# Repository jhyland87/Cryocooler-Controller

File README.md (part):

# ESP32-S3 Cryocooler Controller

Firmware for an ESP32-S3 DevKit that automates the cooldown sequence of a cryogenic cooler. The controller manages a compressor-driven cold stage through ten operational states — from a cold start at room temperature (~295 K) down to an operating setpoint of 78 K, with a graceful shutdown sequence — while enforcing thermal safety limits, detecting back-EMF current spikes, streaming live telemetry via Protobuf over WebSocket, and serving a real-time Preact dashboard over WiFi.

---

## Hardware

| Component | Part | Interface | Address / Pin | Purpose |
|-----------|------|-----------|---------------|---------|
| Microcontroller | ESP32-S3 DevKitC-1-N32R16V | — | — | Host MCU (32 MB flash, 16 MB PSRAM) |
| Cold-stage sensor | ADS1220 + PT1000 RTD | SPI mode 1 (main bus) | CS: decoder Y6 | Cold-stage temperature (4-wire, ratiometric) |
| Waveform generator | AD9837 DDS (AD9833 register set, 16 MHz clock) | SPI (main bus) | FSYNC (CS): decoder Y0 | 60 Hz sine wave for compressor |
| DAC | AD5453 14-bit multiplying | SPI mode 1 (main bus), write only | SYNC: decoder Y1 | Amplifier amplitude control |
| Power monitor | INA239 + 15 mΩ shunt | SPI mode 1 (main bus) | CS: decoder Y2, ALERT: expander GP6 | 12 V rail voltage, current and power |
| IMU | LSM6DSOX on the cryocooler: its own 18 x 18 mm board (`hardware/kicad/imu/`, not yet built) or the Adafruit breakout it replaces | SPI (main bus) via header J14 | CS: decoder Y7, INT1: GPIO 2, INT2: GPIO 39 | Vibration / overstroke detection |
| Fan / pump | 4-pin PWM through a BSS138DW dual driver | LEDC PWM + PCNT tach | PWM: GPIO 9 / 14, tach: GPIO 15 / 21 | Cooling fan + pump |
| Current sensor | ACS37800-015B5 (±15 A) behind an ISOW7741 isolator | SPI mode 3 (main bus, through two gates) | CS: GPIO 17 | Amplifier AC current monitoring |
| Compressor relay | BSS138 → BSS84 high-side +12 V switch (130 mA max) | GPIO | GPIO 16 | Compressor relay on/off |
| Amplifier relay | BSS138 → BSS84 high-side switch | GPIO | GPIO 6 | Amplifier REM line on/off |
| Coolant flow sensor | Alphacool ES (Hall-effect) | GPIO | GPIO 18 | Coolant flow pulses |
| Coolant temperature | NTC thermistor | ADC | GPIO 4 | Coolant temp via voltage divider |
| Status LED | WS2812B-2020 RGB | GPIO | GPIO 38 | Fault / Ready indication |
| Expander | MCP23S08 | SPI (main bus) | CS: decoder Y3 | ±15 V flags, backlight, INA239 ALERT, touch IRQ, 3 spare pins |
| Power button | LTC2954 INT# / KILL# | GPIO | GPIO 1 / GPIO 10 | Button press ramps down, then cuts system power |
| General-purpose I/O | 2-pin headers J16-J20 (signal, GND), each with an LED that follows the pin voltage | GPIO; ADC on IO5 / IO7 only | GPIO 5, 7, 11, 12, 13 | Spare 3.3 V inputs or outputs (sensors, relay triggers, LEDs) |

**I2C:** none. Every peripheral is on SPI or a GPIO.

**Main SPI bus:** CLK → GPIO 42, MOSI → GPIO 41, MISO → GPIO 40. Devices: AD9837, AD5453, the LSM6DSOX (on a cable, header J14), INA239, ADS1220, MCP23S08, display, touch controller and the ACS37800. Their chip selects come from the SN74LVC138A decoder, driven from GPIO 3, 44, 45 and 8. The INA239, ADS1220 and AD5453 use SPI mode 1, and the INA239 and ADS1220 data outputs are high-impedance while CS is high. The ADS1220 DRDY pin is not wired to the MCU.

**ACS37800:** on the main SPI bus, with CS on GPIO 17 (a plain GPIO, not a decoder output). The ACS37800 keeps MISO driven when CS is high, so two SN74LVC1G125 gates connect it only while CS is low: one passes SCK to the isolator, the other passes its MISO to the bus. See [`docs/acs37800.md`](docs/acs37800.md) for its SPI frame and bring-up gotchas.

**General-purpose I/O:** each of the five pins has 100 Ω in series, 200 kΩ to ground (the LED driver's divider) and an ESD clamp, and is 3.3 V only. GPIO 5 and 7 are ADC1 and can read analog with WiFi on; GPIO 11-13 are ADC2, so digital only. The firmware defines the pins (`AUX_IO*_PIN`) but does not use them yet.

**Fan and pump:** each PWM GPIO drives a BSS138 (GPIO high = PWM line low = 0 % drive), because the fan PWM line can reach 5.25 V. A 10 kΩ gate pull-up holds 0 % drive during boot. Each tach line has a 4.7 kΩ series resistor, a clamp on the GPIO side, and a 4.7 kΩ pull-up to 3.3 V.

**INA239 ALERT:** drives its red LED only; it is not wired to the MCU, and the firmware does not read it.

### Circuit board

The 130 x 110 mm 4-layer board is generated from the KiCad schematic in [`hardware/kicad/`](hardware/kicad/README.md). Each module has its own outlined, labelled box on the silkscreen, and the sections with their own supply jumper and LED can be switched off one at a time.

---

## Architecture

All subsystem modules follow a standardised lifecycle pattern built on a CRTP base class (`ModuleBase<T>`) with compile-time interface enforcement. Modules are registered in declarative arrays and initialised/serviced via generic helpers — adding a new module is a one-liner. See [`docs/modules.md`](docs/modules.md) for the full module authoring guide.

```mermaid
flowchart TD
    subgraph Persistent ["Persistent Modules (init once at startup)"]
        HW[hardware<br/>SPI buses]
        IMU[imu<br/>LSM6DSOX accelerometer]
        CMD[commands<br/>Serial console]
        DASH[dashboard<br/>WiFi + Preact SPA + WebSocket]
        TEL[telemetry<br/>Protobuf frame builder]
        SYS[sysinfo<br/>INA239 power monitor]
        OTA[ota<br/>HTTP firmware updates]
    end

    subgraph Control ["Control Modules (re-init on every Initialize state)"]
        COOL[cooling<br/>PWM fan + pump<br/>software LUT]
        CH[cold_head<br/>ADS1220 PT1000 RTD]
        AMP[amplifier<br/>AD9837 + AD5453 DAC + ACS37800]
        COMP[compressor<br/>relay GPIO]
        IND[indicator<br/>WS2812 RGB LED]
    end

    subgraph FSM ["Core Logic"]
        SM[state_machine<br/>Pure FSM — no hardware calls]
    end

    CH  -->|tempC, coolingRate, stalled| SM
    AMP -->|rmsV, overstroke| SM
    IMU -->|overstroke| SM
    SYS -->|sysVoltage| SM

    SM -->|dacTarget| AMP
    SM -->|compressorRelay, amplifierRelay| COMP
    SM -->|faultIndMode, readyIndMode| IND
    SM -->|Output| TEL

    TEL --> DASH
    TEL --> CMD

    classDef persistent fill:#dbeafe,stroke:#3b82f6,color:#1e3a5f
    classDef control    fill:#dcfce7,stroke:#16a34a,color:#14532d
    classDef fsm        fill:#fef3c7,stroke:#d97706,color:#78350f

    class HW,IMU,CMD,DASH,TEL,SYS,OTA persistent
    class COOL,CH,AMP,COMP,IND control
    class SM fsm

    style Persistent fill:#eff6ff,stroke:#93c5fd
    style Control    fill:#f0fdf4,stroke:#86efac
    style FSM        fill:#fffbeb,stroke:#fcd34d
```

---

## Module Reference

### hardware

Initialises the main SPI bus (`SPI.begin(...)`), which the ACS37800 shares.

---

### state_machine

The core of the controller. Ingests sensor readings every tick and outputs a complete set of actuator targets. Contains no hardware calls — pure logic, fully unit-testable on the host PC.

**States:**

| # | Name | Description | FAULT LED | READY LED | DAC |
|---|------|-------------|-----------|-----------|-----|
| -1 | Off | System powered down | Off | Off | 0 |
| 0 | Initialize | Power-up self-check | Solid Amber | Solid Amber | 0 |
| 1 | Idle | Warm standby | Solid Red | Off | 0 |
| 2 | CoarseCooldown | Cooling above 85 K | Flash Fast Red | Off | proportional to temp |
| 3 | FineCooldown | Cooling below 85 K | Flash Fast Red | Flash Slow Green | proportional to temp |
| 4 | Overshoot | Below setpoint, settling | Flash Fast Red | Flash Fast Green | 0 |
| 5 | Settle | In setpoint band; Normal relay | Flash Fast Red | Flash Fast Green | 0 |
| 6 | Baseline | Collecting pre-run baseline (5 min) | Off | Solid Green | 0 |
| 7 | Operating | Normal cryogenic operation | Off | Solid Green | 0 |
| 8 | Shutdown | Graceful shutdown; DAC ramps down | Off | Off | ramps → 0 |
| 9 | Delay | Timed hold; resumes at configured next state | Solid Amber | Solid Amber | 0 |
| 127 | Fault | Terminal fault state | Flash Fast Red | Off | 0 |

**Key configuration** (all in `config.h`):

| Constant | Default | Description |
|----------|---------|-------------|
| `SETPOINT_C` | -195.15 °C (78 K) | Target cold-stage temperature |
| `COARSE_FINE_THRESHOLD_C` | -188.15 °C (85 K) | Coarse/Fine transition boundary |
| `SETPOINT_TOLERANCE_C` | 3.0 °C | Band around setpoint for settle/overshoot logic |
| `SETTLE_DURATION_MS` | 60 000 ms | Time stable before advancing to Baseline |
| `BASELINE_DURATION_MS` | 300 000 ms | Baseline collection window |
| `SHUTDOWN_DURATION_MS` | 5 000 ms | Graceful shutdown ramp duration |
| `STALL_DETECT_WINDOW_MS` | 600 000 ms | Stall detection observation window |
| `STALL_MIN_DROP_C` | 2.0 °C | Minimum temp drop required in the window |
| `BACKOFF_MAX_COUNT` | 10 | Max overstroke events before TooManyBackoffs fault |

---

### cold_head

Reads the PT1000 RTD via the ADS1220 24-bit ADC over SPI (mode 1, chip select GPIO 44). The ADC is configured for 4-wire ratiometric measurement (gain 1, PGA bypassed, 20 SPS with simultaneous 50/60 Hz rejection) with 250 µA IDAC excitation and a 3854 Ω external reference resistor. Raw ADC counts are converted to resistance, then to temperature via the Callendar-Van Dusen equation (above 0 °C) and AN709 polynomial (below 0 °C).

Uses a non-blocking two-phase state machine: start single-shot conversion → wait out the 50 ms conversion time (DRDY is not wired) → read the 24-bit result. Maintains a ring buffer of `TEMP_HISTORY_SIZE` timestamped samples for cooling-rate calculation (°C/min), stall detection, and cooldown progress (0–100 %).

| Function | Returns |
|----------|---------|
| `getLastTempK()` | Cold-stage temperature in Kelvin |
| `getLastTempC()` | Cold-stage temperature in Celsius |
| `getCoolingRateCPerMin()` | °C/min, positive = cooling |
| `isStalled()` | True if stall threshold exceeded |

---

### amplifier

Drives the AD9837 DDS (60 Hz sine wave, through the MD_AD9833 library set to a 16 MHz clock), the AD5453 14-bit multiplying SPI DAC (amplifier amplitude), the amplifier relay (GPIO 6) and the ACS37800 current sensor. Provides two ramp modes:

- `rampToVoltage(target)` — smooth ramp at ±`DAC_MAX_STEP_PER_INTERVAL` per tick
- `rampTowardShutdown(target)` — fast ramp at ±`DAC_SHUTDOWN_STEP_PER_INTERVAL` per tick

**Overstroke (back-EMF) detection:** A slow-tracking EMA forms the baseline. A reading exceeding `baseline + OVERSTROKE_CURRENT_THRESHOLD_A` fires `hasOverstroke()`, subject to `OVERSTROKE_DEBOUNCE_MS`. The EMA is primed for `OVERSTROKE_PRIME_READINGS` ticks on startup.

---

### imu

Drives the LSM6DSOX 6-DOF IMU over SPI (CS GPIO 1) in FIFO mode at 833 Hz. The sensor is mounted on the cryocooler, so it sees the cooler body's vibration. It is cabled to header J14: the IMU board (`hardware/kicad/imu/`, not yet built) or, until then, the Adafruit breakout (product 4438); pinouts are in `hardware/kicad/README.md`. The SPI clock is `LSM6DSOX_SPI_FREQUENCY_HZ`. A missing cable is non-fatal: the module reports unavailable. On `init()` the module sets `I2C_disable` in CTRL4_C (13h) right after the driver's `begin_SPI()`, so the IMU's I²C block ignores traffic for the other devices on the shared SCK/MOSI lines (DS12814 §5.1.1; the driver only disables I3C). The sensor is then configured and a one-time blocking calibration collects samples to compute per-axis offsets (gravity is removed from the Z offset).

Each `service()` call applies calibration offsets, runs a first-order low-pass filter, and computes roll/pitch from filtered acceleration. Motion / overstroke is flagged when acceleration magnitude deviates from 9.81 m/s² by more than `ACCEL_THRESHOLD_MPS2`; it clears after `MOTION_TIMEOUT_MS` of stillness.

A periodic FFT (`calculateFrequency()`) detects the compressor vibration frequency in the 45–75 Hz band using 256 samples at 833 Hz, with Hann windowing and quadratic peak interpolation.

| Function | Returns |
|----------|---------|
| `isInitialized()` | True if sensor was found and configured |
| `hasOverstroke()` | True while motion/overstroke is active |
| `getRoll()` / `getPitch()` | Orientation angles in degrees |
| `getAccelMag()` | Calibrated acceleration magnitude (m/s²) |
| `getFrequencyHz()` | Detected compressor frequency (Hz), or NAN |
| `getTemperature()` | IMU die temperature (°C); mounted on the cooler, this is the cooler-body temperature and also feeds the "ambient" value |

---

### sysinfo

Reads the 12 V rail voltage, current and power from the INA239 power monitor over SPI (15 mΩ shunt, 10 A calibration; GPIO 3 chip select) and exposes `getVoltage()`, `getCurrent()` and `getPower()`. SPI has no ACK, so each tick first reads the INA239 manufacturer and device ID registers; after 3 consecutive failures (for example when 12 V drops) the module disables itself until `reinit`. It also tracks CPU load, heap and PSRAM.

---

### cooling

Controls the cooling fan and pump directly from the ESP32: LEDC generates 25 kHz PWM and PCNT counts the tach pulses. Also samples the Alphacool ES flow sensor and NTC coolant temperature.

**Software LUT:** Each channel has an independently-configured temperature-to-duty lookup table with hysteresis, evaluated once per second from coolant temperature. Entries are sorted ascending by temperature; the evaluator only writes to the chip when the active row changes.

**Fault detection:** A channel with drive applied and no tach pulses for `COOLING_TACH_STALL_MS` raises `hasFanFault()`. It is reported in telemetry and logs and does not fault the state machine.

**Pump normalisation:** User-facing pump speeds are 0–100 % normalised, mapped to 0–`COOLING_PUMP_MAX_DUTY_PCT` (raw 0–255) at the hardware boundary. The pump stalls above ~16 % effective duty (~4400 RPM).

**Tracking monitors:** Score-based monitors for fan duty, coolant temperature, and flow rate detect sustained deviations from expected values.

| Function | Returns |
|----------|---------|
| `getCoolantTemperature()` | Coolant temperature in °C |
| `getCoolantFlowRate()` | Coolant flow rate in L/min |
| `getFanSpeed()` | Fan duty (0–255) |
| `getFanRPM()` | Fan tachometer RPM |
| `getPumpSpeed()` | Pump speed (normalised 0–100 %) |
| `getPumpRPM()` | Pump tachometer RPM |
| `hasFanFault()` | True while a driven channel has no tach pulses |
| `getFanFaultDurationMs()` | Duration of current fault episode |

---

### compressor

Manages the compressor relay (GPIO 16 → high-side +12 V switch) with timed-run support. `compressor start <duration>` energises the relay for a specified duration (e.g. `1h30m`, `45s`), clamped to `COMPRESSOR_MAX_RUN_MS`. Can be disabled at compile time with `ENABLE_COMPRESSOR false`.

---

### indicator

Drives the on-board WS2812 RGB LED (GPIO 38) according to the state machine's requested `Mode`. All flash timing is non-blocking — `update(nowMs)` is called every loop iteration.

| Mode | Colour | Rate |
|------|--------|------|
| `SolidRed` | Red | — |
| `SolidGreen` | Green | — |
| `SolidAmber` | Amber | — |
| `FlashFastRed` | Red | 2 Hz |
| `FlashSlowGreen` | Green | 1 Hz |
| `FlashFastGreen` | Green | 2 Hz |

---

### dashboard

Connects to WiFi and serves a Preact single-page application with real-time telemetry:

- **HTTP** (port 80): serves the embedded SPA (`index.html`, `app.js`, `style.css`) and a JSON telemetry endpoint at `GET /api/telemetry`
- **WebSocket** (`ws://<hostname>/ws` on port 80): streams Protobuf-encoded telemetry frames at 1 Hz
- **mDNS**: `cryocooler.local`

The dashboard frontend uses Preact + MUI + Vite and is bundled into firmware flash at build time via `scripts/embed_web.py`. WiFi credentials live in `include/config/arduino_secrets.h`.

---

### ota

HTTP OTA firmware update endpoint. `GET /ota` serves an upload form; `POST /ota` flashes new firmware. Enabled with `ENABLE_OTA true` in `config.h`.

---

### commands

Non-blocking USB serial command handler. `service()` accumulates characters and dispatches completed lines. The same `processLine()` function is used by the TCP server and by unit tests with a stub `Print`.

| Command | Action |
|---------|--------|
| `start` | Begin cooldown (from Off or Idle) |
| `stop` | Abort and return to Idle |
| `off` | Power off the system entirely |
| `reboot` | Reboot the MCU |
| `status` | Print current state and running flag |
| `summary` | Full snapshot of all sensor and actuator values |
| `fsm state` | Print current FSM state with time-in-state |
| `fsm history` | Print recent FSM state transitions |
| `fault clear` | Clear an active fault and return to Idle |
| `fault push` | Push a fault record |
| `fault history` | Print fault log with reason and clear method |
| `board` | Print compile-time board/platform info |
| `reinit` | Re-initialise all or named modules |
| `wifi status` | Print WiFi link, signal, TX power and last disconnect reason |
| `wifi retry` | Start a new WiFi connection attempt now |
| `wifi txpower <dBm>` | Set max WiFi TX power until reboot; retries if not connected |
| `cooling on/off` | Enable / disable cooling system |
| `cooling fan <N>` | Set fan: raw duty (0–255) or percent (0–100%) |
| `cooling pump <N>` | Set pump: raw duty (0–255) or percent (0–100%) |
| `set vout <V>` | Set DAC output voltage (0–120 V, 0–100 %, or `auto`) |
| `dac raw <N>` | Raw SPI write to the AD5453 (0–16383), bypassing firmware DAC management |
| `get vout` | Get current DAC output voltage |
| `relay` | Show current state of both relays |
| `relay amplifier on/off` | Control amplifier relay |
| `relay compressor on/off` | Control compressor relay |
| `compressor start <dur>` | Start timed compressor run (e.g. `1h30m`) |
| `compressor status` | Show compressor state and remaining time |
| `compressor stop` | Stop the compressor immediately |
| `telemetry on/off` | Enable / disable telemetry output |
| `telemetry serial on/off` | Enable / disable the tab-delimited telemetry dump on USB Serial (off by default) |
| `telemetry delta on/off` | Delta-only or full frames for the serial dump |
| `dashboard on/off` | Enable / disable dashboard WebSocket broadcasts |
| `mock ...` | Sensor mock: `enable`, `disable`, `status`, `temp`, etc. |
| `log level <L>` | Set runtime log level (0–5 or off/error/warn/info/debug/verbose) |
| `shutdown` | Shut the system down |
| `ota status` | Print OTA partition and firmware version info |
| `update image` | Flash new firmware via HTTP upload |
| `help` | List all commands |

---

### telemetry

Snapshots all module values each tick into a `FrameBuilder`. The WebSocket path encodes frames as Protobuf binary via Nanopb; the HTTP `/api/telemetry` endpoint returns JSON. The schema source of truth is `proto/telemetry.proto`.

---

### frame_builder

Format-agnostic telemetry frame with a fluent field API. Renders to a tab-delimited serial line or `JsonDocument` from the same snapshot.

---

### conversions

Header-only pure-math utilities with no hardware dependencies — safe for native unit tests.

| Function | Description |
|----------|-------------|
| `resistanceToTemperaturePT1000(R)` | PT1000 Ω → °C (Callendar-Van Dusen / AN709) |
| `tempCToDacValue(...)` | Temperature → 12-bit DAC mapping |
| `tempCToFraction(...)` | Temperature → cooldown fraction [0.0, 1.0] |
| `msToHHMMSS(ms, buf)` | ms → `HH:MM:SS` string |
| `parseDurationMs(str, ...)` | Human duration string → ms (e.g. `1h30m`) |
| `formatDurationMs(ms, buf, len)` | ms → compact human string (e.g. `1h 30m 00s`) |

---

### sensor_mock

Injects synthetic sensor values into all modules for hardware-free FSM testing. When `sensor_mock::isActive()`, `read()`/`service()` in each module pull from `sensor_mock::get()` instead of hardware. Activated via the `mock` serial command.

---

## Transition Triggers

### Normal Operation Flow

`start()` selects the resume state from `tempK` and is valid from both **Off** and **Idle**. `Delay` is reachable from any non-Fault state via `startDelay()` — see [Global Transitions](#global-transitions).

```mermaid
stateDiagram-v2
    direction TB

    [*] --> Off
    Off  --> Initialize : reinit
    Idle --> Initialize : reinit
    Initialize --> Idle : init timer

    state "Cooldown Phase" as COOLDOWN {
        CoarseCooldown --> FineCooldown : temp < 85 K
        FineCooldown --> CoarseCooldown : temp > 85 K
    }

    state "Approaching Setpoint" as SETTLING {
        Overshoot --> Settle : in band
    }

    state "Stable Operation" as STABLE {
        Baseline --> Operating : baseline timer
    }

    Idle --> CoarseCooldown : start, temp <br/>≥ 85 K
    Idle --> FineCooldown   : start, below <br/>85 K
    Idle --> Overshoot      : start, below<br/> setpoint
    Idle --> Settle         : start, in band

    FineCooldown --> Overshoot : below setpoint
    FineCooldown --> Settle    : in band

    Settle --> Baseline : settle timer

    COOLDOWN --> Shutdown : stop
    SETTLING --> Shutdown : stop
    STABLE   --> Shutdown : stop
    Delay    --> Shutdown : stop
    Shutdown --> Idle     : shutdown<br/>timer

    Delay --> Idle           : timer → Idle
    Delay --> CoarseCooldown : timer → Coarse

    classDef startup  fill:#dbeafe,color:#1e3a5f
    classDef cooldown fill:#ccfbf1,color:#134e4a
    classDef settling fill:#fef3c7,color:#78350f
    classDef stable   fill:#dcfce7,color:#14532d
    classDef shutdown fill:#f1f5f9,color:#334155
    classDef delay    fill:#ede9fe,color:#3b0764

    class Off,Initialize,Idle startup
    class CoarseCooldown,FineCooldown cooldown
    class Overshoot,Settle settling
    class Baseline,Operating stable
    class Shutdown shutdown
    class Delay delay
```

### Fault Conditions

```mermaid
stateDiagram-v2
    direction LR

    state "Cooldown Phase" as COOLDOWN {
        CoarseCooldown
        FineCooldown
    }

    state "Approaching Setpoint" as SETTLING {
        Overshoot
        Settle
    }

    state "Stable Operation" as STABLE {
        Baseline
        Operating
    }

    COOLDOWN --> Fault : temp stall
    COOLDOWN --> Fault : too many backoffs
    SETTLING --> Fault : too many backoffs
    STABLE   --> Fault : too many backoffs
    Delay    --> Fault : too many backoffs

    Fault --> Idle       : clearFault()
    Fault --> Initialize : reinit()

    classDef cooldown fill:#ccfbf1,color:#134e4a
    classDef settling fill:#fef3c7,color:#78350f
    classDef stable   fill:#dcfce7,color:#14532d
    classDef delay    fill:#ede9fe,color:#3b0764
    classDef fault    fill:#fee2e2,stroke:#ef4444,color:#7f1d1d
    classDef startup  fill:#dbeafe,color:#1e3a5f

    class CoarseCooldown,FineCooldown cooldown
    class Overshoot,Settle settling
    class Baseline,Operating stable
    class Delay delay
    class Fault fault
    class Idle,Initialize startup
```

### Global Transitions

These originate from all non-Fault states and are omitted from the diagrams above.

| Trigger | Condition | To |
|---------|-----------|-----|
| `off()` | — | Off |
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
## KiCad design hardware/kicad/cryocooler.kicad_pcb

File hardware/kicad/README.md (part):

# Cryocooler controller — KiCad schematic

KiCad 10 hierarchical schematic for the ESP32-S3 cryocooler controller. Open
`cryocooler.kicad_pro`. A PDF export is in `cryocooler-schematic.pdf`. The 4-layer board is `cryocooler.kicad_pcb` (see [PCB layout](#pcb-layout)).

GPIO assignments follow [`include/config/pin_config.h`](../../include/config/pin_config.h).
The top-level README hardware table was brought in line with these sheets and the firmware
on 2026-10-14; if the two ever disagree, the schematic and `pin_config.h` win.

## Sheets

| Sheet | Contents |
|---|---|
| `cryocooler.kicad_sch` (root) | ESP32-S3-WROOM-2-N32R16V, EN/BOOT, USB-C (GCT USB4205-GF-A, flag type) + ESD |
| `power_input` | 12 V DC jack (5.5 x 2.1 mm), 5 A fuse, SMBJ16A TVS, bulk caps |
| `power_button` | LTC2954CDDB-2 (INT# to GPIO1), AONR21307 high-side P-FET with slow-start gate network and 15 V clamp, KILL# bias, red standby LED through 13 kΩ and one BSS138, TPD1E05U06 on the button line `PWR_BTN` (SW3 only; the J7 panel header went in rev 4) |
| `rails_logic` | AP63205 buck with SRP4020TA-4R7M (12→5 V); TPS2116 selects +5V or USB VBUS into +5V_OR, priority to the 12 V side → TPS62822 buck with SRP4020TA-R47M (→3.3 V) |
| `rails_15v` | ADP5071ACPZ dual converter at 1.2 MHz with SRP7050TA-3R3M and -6R8M (rev 1 values) → one LT3097 dual LDO (±14.7 V, 147 kΩ SET resistors); the LT3097 PGP / PGN go to the `power_good` sheet |
| `power_good` | One node and green LED per LT3097 PG pin (with a 470 k / 470 k guard and BSS138W so a missing -15 V pulls `PGN_15V` low), a BAT54AW AND of the two nodes into `PG_15V`, and the 3.3 V flag `PG_15V_N` on GPIO43 (low = both ±15 V rails good); both flags are also read by the MCP23S08 |
| `signal_gen` | ECS-2520MV 16 MHz oscillator, AD9837 (LFCSP-10), OPA2991 dual U5 (A: gain 16.3; B: AD5453 output stage, 22 pF C1), R39 + MMBZ9V1 clamp into AD5453 VREF, AD5453 (decoder Y1); all digital parts on `+3V3_SG` |
| `amp_control` | GPIO6 → BSS138 → BSS84 high-side 12 V to amplifier REM, red/green LED; a second BSS138 (Q9) in series with the level shifter's source is gated by `PG_15V`, so REM cannot turn on unless both ±15 V rails are good |
| `amp_current` | ACS37800-015B5 (SPI, ±15 A at 5 V) + ISOW7741 (isolated 5 V and SPI in one part) with FB1 / FB2, 4×1 MΩ + 4.02 kΩ divider, TE 2305908-2 SMT pluggable header J11, TE 643228-1 through-hole header J12. Rev 4: on the shared SPI bus through two SN74LVC1G125 gates enabled by `ACS_CS` (U41 passes SCK in, U42 passes MISO out), with 10 kΩ pull-ups on the gated SCK and on `ACS_CS` |
| `system_current` | INA239 (SPI mode 1, decoder Y2) + 15 mΩ shunt in the switched 12 V rail, 49.9 Ω / 470 nF input filter, ALERT to expander GP6, ALERT and 3V3 power LEDs |
| `gpio_expander` ("GPIO Expander") | MCP23S08 QFN-20 on the shared SPI bus (mode 0, decoder Y3), on unswitched `+3V3`: GP0-1 power-good flags, GP4 display backlight enable, GP6 INA239 ALERT, GP7 touch IRQ, GP2/GP3/GP5 spare; RESET tied to +3V3, A0/A1 and exposed pad to GND, INT to a test point |
| `cooling` ("Water Cooling") | Fan and pump: LEDC PWM through the two halves of one BSS138DW (Q61) as open-drain drivers (gates held on by 10 kΩ to `+3V3`, so 0% drive at reset), tach through 4.7 kΩ to PCNT; Alphacool ES flow tach and NTC; connector-side pull-ups sit on the switched `+3V3_COOL` rail. Rev 4: XKB X2510WRS headers (J5 is a 4-pin part with pin 4 unused), 4.7 kΩ and 10 kΩ resistors in arrays RN1 / RN2 |
| `cold_head` ("Cold Head Temp") | ADS1220 (SPI mode 1, CS on GPIO44), 4-wire PT1000, 3.9 kΩ Rref, DRDY pull-up + test point; powered from the switched `+3V3_CH` rail |
| `imu` | J14, a Molex Micro-Lock Plus 2x4 header (505448-0891, 1.25 mm, right angle, positive lock) for the off-board Adafruit LSM6DSOX module: SPI bus, CS, INT1/INT2, +3V3, GND; one NUF6401MN six-channel filter (100 Ω series, 17 pF and ESD clamp each side) |
| `compressor_relay` | GPIO16 → BSS138 → BSS84 high-side +12 V switch, flyback diode, red/green state LED, 2-pin right-angle XKB X2510WRS-02 output |
| `indicators` | WS2812B-2020 status LED behind a 74AHCT1G125 level shifter |
| `debug` | Test points on rails, grounds and control lines; LEDs on +5V and ISO 5V |
| `supply_switches` | 5 Keystone 5110 0603 zero-ohm jumpers JP1-JP5, one per section, in series with that section's supply (see "Supply jumpers" below); FB3 ahead of JP5 |
| `display` | FH12-14S FPC (J15) to the Phoenix 2.4" ST7789V touch display in the UCS 125-87-F-GD-D2,4 lid (pinout from datasheet 109921), TSC2046 touch controller on the shared SPI bus, BSS138 backlight switch (+5 V through 39 Ω), 10 kΩ pull-downs on the GPIO45 / GPIO46 straps |
| `aux_io` ("General Purpose IO") | Rev 4: GPIO 5, 7, 11, 12, 13 each on a 2-pin XKB X2510WRS-02 header J16-J20 (signal, GND) with an ESD clamp, 100 Ω in series and a 100 kΩ / 100 kΩ divider to GND; one OPA4990 section per pin (on `+5V_OR`, so it also runs on USB power) takes the divider tap and drives a green LED with Vpin / 6.6 kΩ |

## ±15 V rails and power good

The ADP5071 makes the two pre-regulated rails from `+5V_PS15` at 1.2 MHz (SYNC/FREQ low), with SEQ to VREG for a
simultaneous start and SLEW to AGND for the slowest, quietest edges. One LT3097 post-regulates them to **±14.7 V**
(V = 100 µA × R_SET, 147 kΩ; +15 V would sit at the top of the LT3097's 0–15 V positive range, so the nets keep their
`+15V` / `-15V` names but run about 0.3 V low). The compensation and feedback values are from rev 1; check the loops on the
bench.

`PGP_15V` and `PGN_15V` go to MCP23S08 GP0 and GP1, and the amplifier module logs which rail changed
(`amplifier::railFlags()`).

PGP and PGN are open-collector (low = bad). Each drives its own node (`PGP_15V`, `PGN_15V`): +15 V through
220 kΩ / 62 kΩ, about 3.2 V when its rail is good and 0 V when its pin pulls low or the rail is missing (thresholds
from the 432 kΩ / 10 kΩ PGFB dividers, about 13.3 V). Each node turns on a BSS138W that lights its green LED (D11
for +15 V, D12 for −15 V). A BAT54AW (common anode) with a 10 kΩ pull-up to +3V3 ANDs the nodes into `PG_15V`
(3.3 V only when both are good). `PG_15V` gates Q9 (a series BSS138 in the amplifier REM switch) and Q10 (the
`PG_15V_N` flag for GPIO43). The amplifier module logs every change of `PG_15V_N` (they show in the dashboard
console); the firmware should still check it before starting the signal generator.

## GPIO map (ESP32-S3-WROOM-2)

| Signal | GPIO | Signal | GPIO |
|---|---|---|---|
| CS decoder enable / fan PWM | 8 / 9 | CS decoder A / B / C | 3 / 44 (RXD0) / 45 |
| SPI SCK / MOSI / MISO | 42 / 41 / 40 | General-purpose I/O (J16-J20) | 5, 7 (ADC1), 11, 12, 13 (ADC2) |
| LSM6DSOX INT1 / INT2 | 2 / 39 | ACS37800 CS (shared SPI bus) | 17 |
| Amp REM enable | 6 | PWR_KILL (LTC2954 KILL#) | 10 |
| PWR_INT (LTC2954 INT#) | 1 | Flow tach | 18 |
| Pump PWM / fan tach | 14 / 15 | NTC ADC | 4 |
| Pump tach | 21 | Free | 47 (1.8 V) |
| Status RGB (WS2812B-2020) | 38 | Compressor relay enable | 16 |
| Display D/C | 48 | Display RESET | 46 (strap, 10 kΩ pull-down) |

The shared-bus chip selects come from U32 (SN74LVC138A): Y0 AD9837, Y1 AD5453, Y2 INA239, Y3 MCP23S08, Y4 display, Y5 touch, Y6 ADS1220, Y7 LSM6DSOX. Firmware numbers them `CS_ID_BASE + Yn` (`pin_config.h`, `src/spi_select.cpp`).

GPIO3 is a strapping pin (JTAG source); R17 (10 kΩ) on CS_ADDR_A keeps it high at reset, which selects the default USB-JTAG. R19 (10 kΩ) on CS_ADDR_C holds strap GPIO45 low, and R18 (10 kΩ) on CS_EN_N keeps the decoder off until firmware runs. The INA239 ALERT pin drives only its LED. GPIO43 (TXD0) toggles with ROM boot messages, so it carries no chip select; it reads the active-low `PG_15V_N` power-good flag through a 1 kΩ series resistor (`PG_15V_N_PIN`). ACS37800 chip-select is on GPIO17. GPIO26–37 are reserved
by the octal flash/PSRAM and are left unconnected.

## Drawing conventions

Power symbols are always upright (supplies point up, grounds hang down) and resistors use the US zig-zag symbol
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
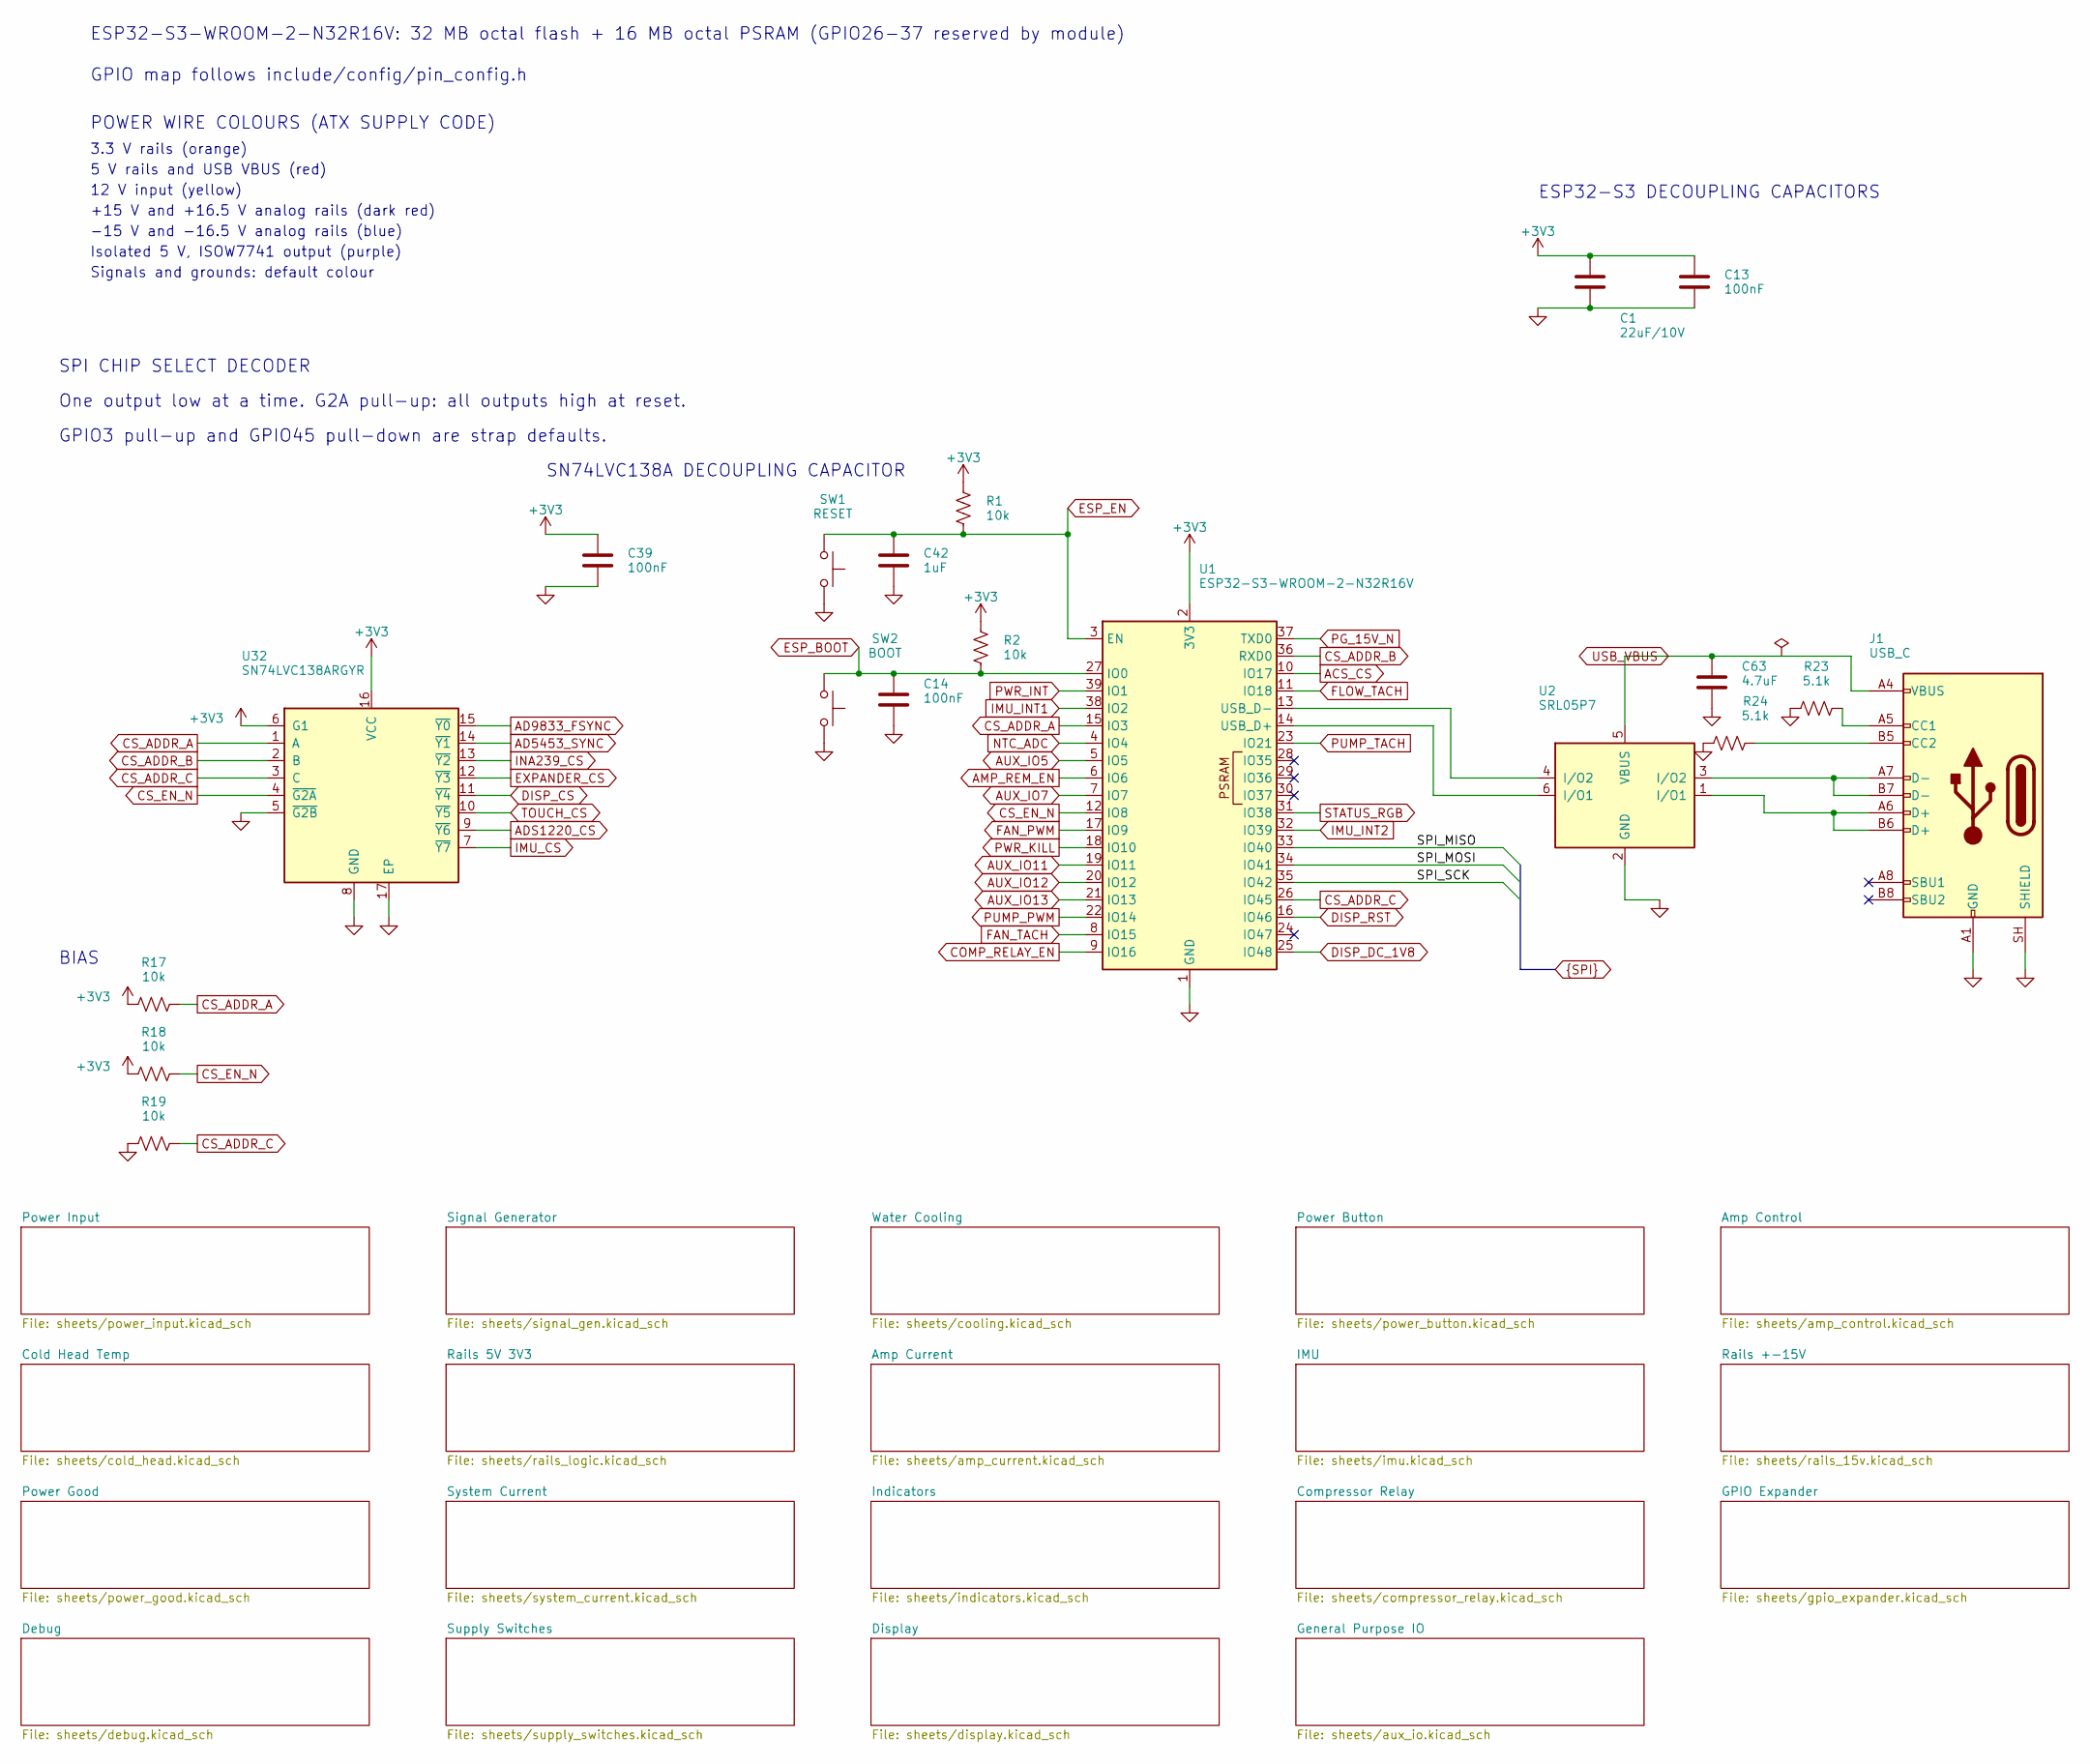
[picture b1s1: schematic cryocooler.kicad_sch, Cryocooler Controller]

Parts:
C1: 22uF/10V; C_1206_3216Metric
C13, C14, C39: 100nF; C_0402_1005Metric
C42: 1uF; C_0603_1608Metric
C63: 4.7uF; C_0805_2012Metric
J1: USB_C; USB_C_Receptacle_GCT_USB4205-GF-A_16P_Flag
R1, R2, R17, R18, R19: 10k; R_0402_1005Metric
R23, R24: 5.1k; R_0402_1005Metric
SW1: RESET; SW_Panasonic_EVP-AA
SW2: BOOT; SW_Panasonic_EVP-AA
U1: ESP32-S3-WROOM-2-N32R16V; ESP32-S3-WROOM-2
U2: SRL05P7; MCC_DFN1510-6_1.5x1.0mm_P0.5mm
U32: SN74LVC138ARGYR; Texas_RGY_R-PVQFN-N16_EP2.05x2.55mm

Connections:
+3V3: C1.1, C13.1, C39.1, R1.1, R2.1, R17.1, R18.1, U1.2 (3V3), U32.6 (G1), U32.16 (VCC); also elsewhere on the board
ACS_CS: U1.10 (IO17); also elsewhere on the board
AD5453_SYNC: U32.14 (~Y1); also elsewhere on the board
AD9833_FSYNC: U32.15 (~Y0); also elsewhere on the board
ADS1220_CS: U32.9 (~Y6); also elsewhere on the board
AMP_REM_EN: U1.6 (IO6); also elsewhere on the board
AUX_IO5: U1.5 (IO5); also elsewhere on the board
AUX_IO7: U1.7 (IO7); also elsewhere on the board
AUX_IO11: U1.19 (IO11); also elsewhere on the board
AUX_IO12: U1.20 (IO12); also elsewhere on the board
AUX_IO13: U1.21 (IO13); also elsewhere on the board
COMP_RELAY_EN: U1.9 (IO16); also elsewhere on the board
CS_ADDR_A: R17.2, U1.15 (IO3), U32.1 (A)
CS_ADDR_B: U1.36 (RXD0), U32.2 (B)
CS_ADDR_C: R19.2, U1.26 (IO45), U32.3 (C)
CS_EN_N: R18.2, U1.12 (IO8), U32.4 (~G2A)
DISP_CS: U32.11 (~Y4); also elsewhere on the board
DISP_DC_1V8: U1.25 (IO48); also elsewhere on the board
DISP_RST: U1.16 (IO46); also elsewhere on the board
ESP_BOOT: C14.1, R2.2, SW2.1, U1.27 (IO0)
ESP_EN: C42.1, R1.2, SW1.1, U1.3 (EN)
EXPANDER_CS: U32.12 (~Y3); also elsewhere on the board
FAN_PWM: U1.17 (IO9); also elsewhere on the board
FAN_TACH: U1.8 (IO15); also elsewhere on the board
FLOW_TACH: U1.11 (IO18); also elsewhere on the board
GND: C1.2, C13.2, C14.2, C39.2, C42.2, C63.2, J1.A1 (GND), J1.A12 (GND), J1.B1 (GND), J1.B12 (GND), J1.SH (SHIELD), R19.1, R23.1, R24.1, SW1.2, SW2.2, U1.1 (GND), U1.40 (GND), U1.41 (GND), U2.2 (GND), U32.5 (~G2B), U32.8 (GND), U32.17 (EP); also elsewhere on the board
IMU_CS: U32.7 (~Y7); also elsewhere on the board
IMU_INT1: U1.38 (IO2); also elsewhere on the board
IMU_INT2: U1.32 (IO39); also elsewhere on the board
INA239_CS: U32.13 (~Y2); also elsewhere on the board
NTC_ADC: U1.4 (IO4); also elsewhere on the board
unnamed: J1.A5 (CC1), R23.2
unnamed: J1.B5 (CC2), R24.2
unnamed: J1.A6 (D+), J1.B6 (D+), U2.1 (I/O1)
unnamed: J1.A7 (D-), J1.B7 (D-), U2.3 (I/O2)
unnamed: U1.14 (USB_D+), U2.6 (I/O1)
unnamed: U1.13 (USB_D-), U2.4 (I/O2)
PG_15V_N: U1.37 (TXD0); also elsewhere on the board
PUMP_PWM: U1.22 (IO14); also elsewhere on the board
PUMP_TACH: U1.23 (IO21); also elsewhere on the board
PWR_INT: U1.39 (IO1); also elsewhere on the board
PWR_KILL: U1.18 (IO10); also elsewhere on the board
SPI_MISO: U1.33 (IO40); also elsewhere on the board
SPI_MOSI: U1.34 (IO41); also elsewhere on the board
SPI_SCK: U1.35 (IO42); also elsewhere on the board
STATUS_RGB: U1.31 (IO38); also elsewhere on the board
TOUCH_CS: U32.10 (~Y5); also elsewhere on the board
USB_VBUS: C63.1, J1.A4 (VBUS), J1.A9 (VBUS), J1.B4 (VBUS), J1.B9 (VBUS), U2.5 (VBUS); also elsewhere on the board

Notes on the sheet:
GPIO map follows include/config/pin_config.h
ESP32-S3-WROOM-2-N32R16V: 32 MB octal flash + 16 MB octal PSRAM (GPIO26-37 reserved by module)
Signals and grounds: default colour
+15 V and +16.5 V analog rails (dark red)
5 V rails and USB VBUS (red)
Isolated 5 V, ISOW7741 output (purple)
SN74LVC138A DECOUPLING CAPACITOR
ESP32-S3 DECOUPLING CAPACITORS
GPIO3 pull-up and GPIO45 pull-down are strap defaults.
POWER WIRE COLOURS (ATX SUPPLY CODE)
BIAS
-15 V and -16.5 V analog rails (blue)
SPI CHIP SELECT DECODER
12 V input (yellow)
One output low at a time. G2A pull-up: all outputs high at reset.
3.3 V rails (orange)

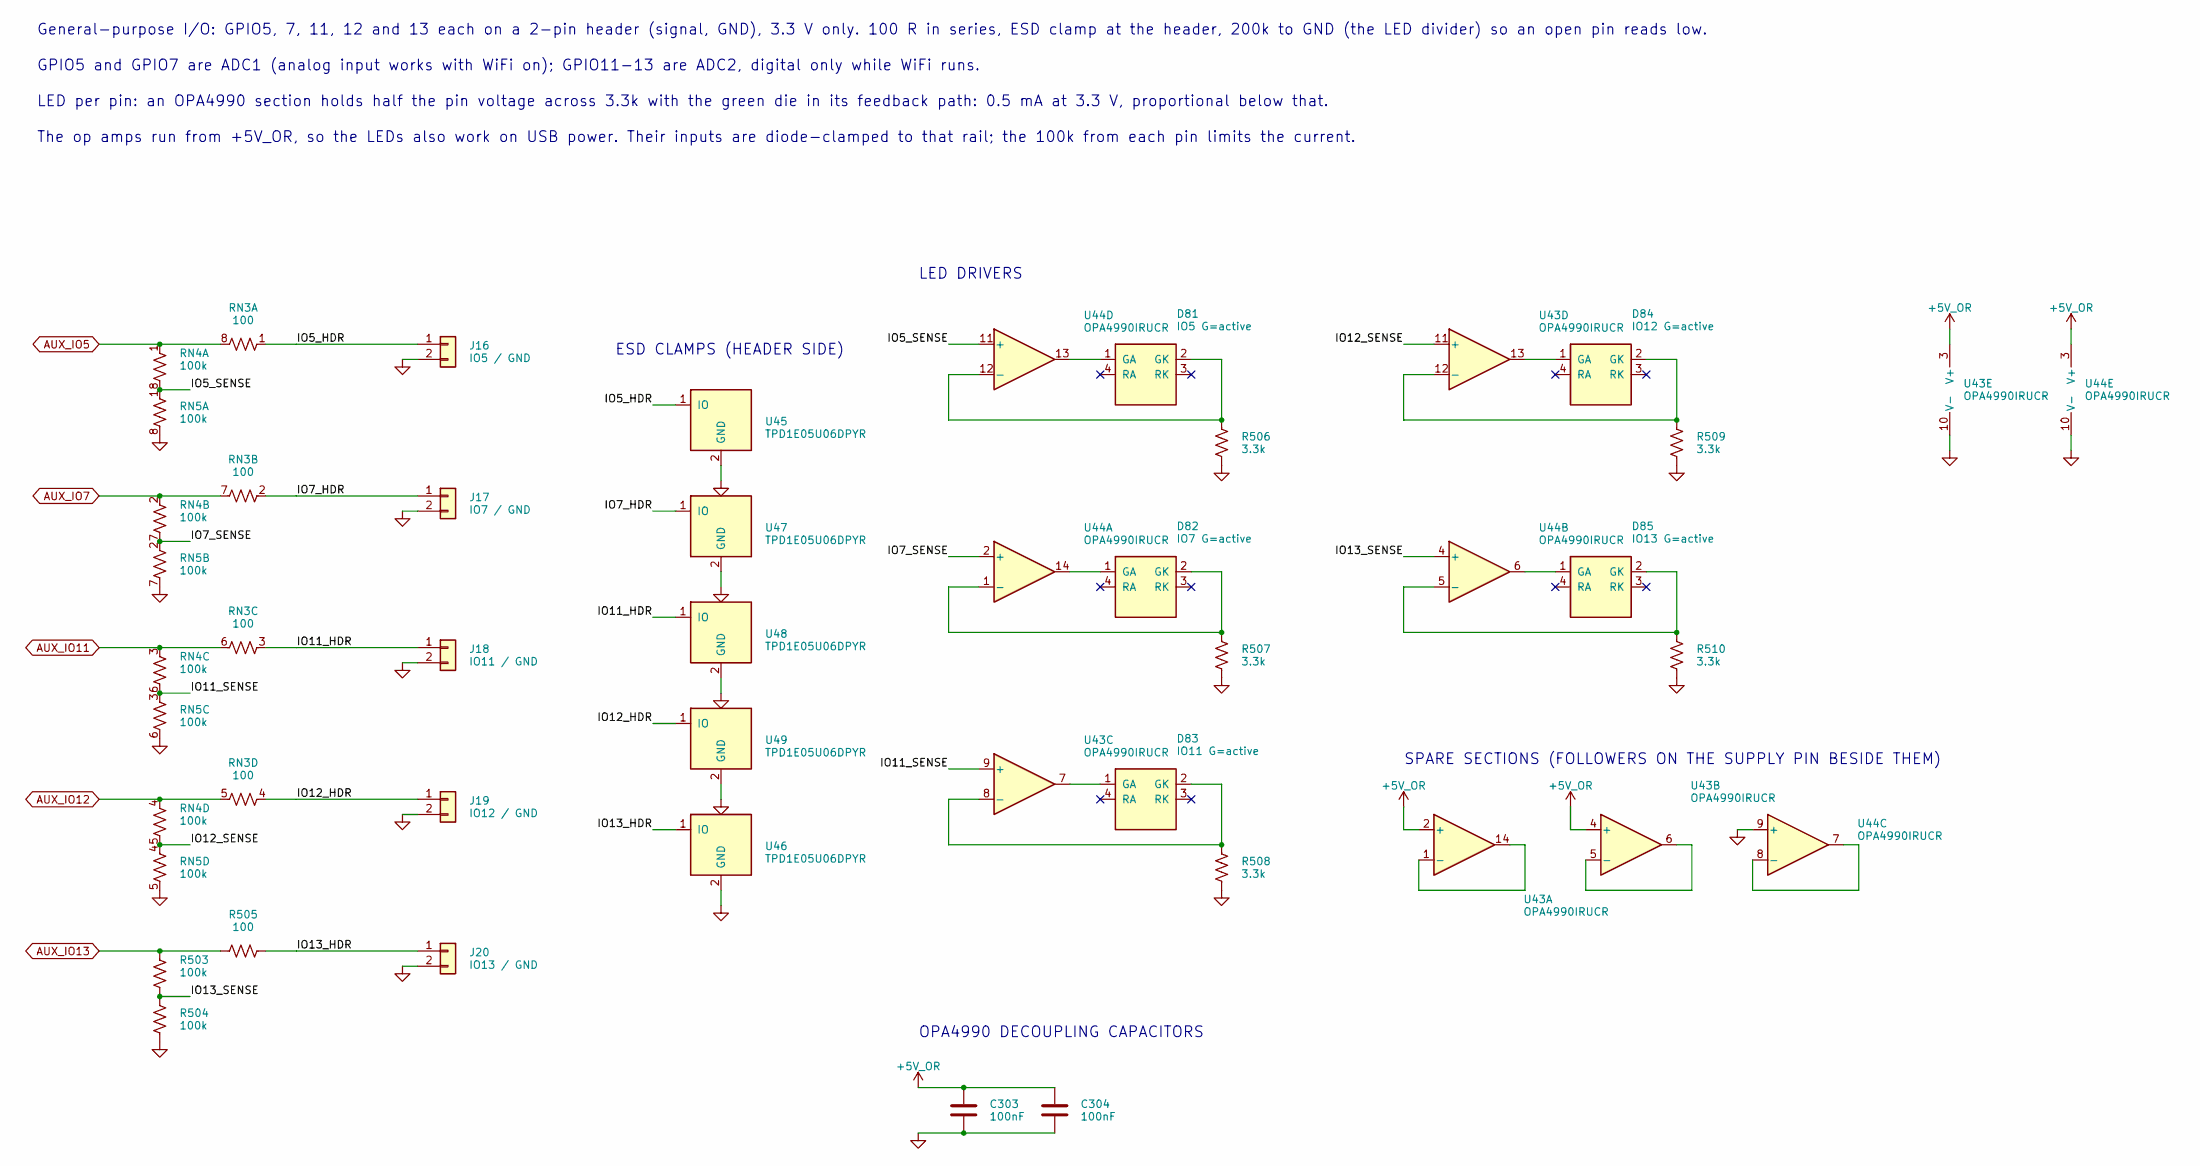
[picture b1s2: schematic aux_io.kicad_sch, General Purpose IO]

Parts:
C303, C304: 100nF; C_0402_1005Metric
D81: IO5 G=active; LED_Kingbright_APGB0607
D82: IO7 G=active; LED_Kingbright_APGB0607
D83: IO11 G=active; LED_Kingbright_APGB0607
D84: IO12 G=active; LED_Kingbright_APGB0607
D85: IO13 G=active; LED_Kingbright_APGB0607
J16: IO5 / GND; XKB_X2510WRS-02-9TSN_1x02_P2.54mm_Horizontal
J17: IO7 / GND; XKB_X2510WRS-02-9TSN_1x02_P2.54mm_Horizontal
J18: IO11 / GND; XKB_X2510WRS-02-9TSN_1x02_P2.54mm_Horizontal
J19: IO12 / GND; XKB_X2510WRS-02-9TSN_1x02_P2.54mm_Horizontal
J20: IO13 / GND; XKB_X2510WRS-02-9TSN_1x02_P2.54mm_Horizontal
R503, R504: 100k; R_0402_1005Metric
R505: 100; R_0402_1005Metric
R506, R507, R508, R509, R510: 3.3k; R_0402_1005Metric
RN3: 100; R_Array_Convex_4x0402
RN4, RN5: 100k; R_Array_Convex_4x0402
U43, U44: OPA4990IRUCR; Texas_S-PX2QFN-14
U45, U46, U47, U48, U49: TPD1E05U06DPYR; Texas_DPY0002A_0.6x1mm_P0.65mm

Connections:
+5V_OR: C303.1, C304.1, U43.2 (+), U43.3 (V+), U43.4 (+), U44.3 (V+); also elsewhere on the board
/General Purpose IO/IO5_HDR: J16.1, RN3.1 (R1.1), U45.1 (IO)
/General Purpose IO/IO5_SENSE: RN4.8 (R1.2), RN5.1 (R1.1), U44.11 (+)
/General Purpose IO/IO7_HDR: J17.1, RN3.2 (R2.1), U47.1 (IO)
/General Purpose IO/IO7_SENSE: RN4.7 (R2.2), RN5.2 (R2.1), U44.2 (+)
/General Purpose IO/IO11_HDR: J18.1, RN3.3 (R3.1), U48.1 (IO)
/General Purpose IO/IO11_SENSE: RN4.6 (R3.2), RN5.3 (R3.1), U43.9 (+)
/General Purpose IO/IO12_HDR: J19.1, RN3.4 (R4.1), U49.1 (IO)
/General Purpose IO/IO12_SENSE: RN4.5 (R4.2), RN5.4 (R4.1), U43.11 (+)
/General Purpose IO/IO13_HDR: J20.1, R505.2, U46.1 (IO)
/General Purpose IO/IO13_SENSE: R503.2, R504.1, U44.4 (+)
AUX_IO5: RN3.8 (R1.2), RN4.1 (R1.1); also elsewhere on the board
AUX_IO7: RN3.7 (R2.2), RN4.2 (R2.1); also elsewhere on the board
AUX_IO11: RN3.6 (R3.2), RN4.3 (R3.1); also elsewhere on the board
AUX_IO12: RN3.5 (R4.2), RN4.4 (R4.1); also elsewhere on the board
AUX_IO13: R503.1, R505.1; also elsewhere on the board
GND: C303.2, C304.2, J16.2, J17.2, J18.2, J19.2, J20.2, R504.2, R506.2, R507.2, R508.2, R509.2, R510.2, RN5.5 (R4.2), RN5.6 (R3.2), RN5.7 (R2.2), RN5.8 (R1.2), U43.10 (V-), U44.9 (+), U44.10 (V-), U45.2 (GND), U46.2 (GND), U47.2 (GND), U48.2 (GND), U49.2 (GND); also elsewhere on the board
unnamed: D81.1 (GA), U44.13
unnamed: D81.2 (GK), R506.1, U44.12 (-)
unnamed: D82.1 (GA), U44.14
unnamed: D82.2 (GK), R507.1, U44.1 (-)
unnamed: D83.1 (GA), U43.7
unnamed: D83.2 (GK), R508.1, U43.8 (-)
unnamed: D84.1 (GA), U43.13
unnamed: D84.2 (GK), R509.1, U43.12 (-)
unnamed: D85.1 (GA), U44.6
unnamed: D85.2 (GK), R510.1, U44.5 (-)
unnamed: U43.1 (-), U43.14
unnamed: U43.5 (-), U43.6
unnamed: U44.7, U44.8 (-)

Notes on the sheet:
GPIO5 and GPIO7 are ADC1 (analog input works with WiFi on); GPIO11-13 are ADC2, digital only while WiFi runs.
General-purpose I/O: GPIO5, 7, 11, 12 and 13 each on a 2-pin header (signal, GND), 3.3 V only. 100 R in series, ESD clamp at the header, 200k to GND (the LED divider) so an open pin reads low.
SPARE SECTIONS (FOLLOWERS ON THE SUPPLY PIN BESIDE THEM)
LED DRIVERS
LED per pin: an OPA4990 section holds half the pin voltage across 3.3k with the green die in its feedback path: 0.5 mA at 3.3 V, proportional below that.
OPA4990 DECOUPLING CAPACITORS
The op amps run from +5V_OR, so the LEDs also work on USB power. Their inputs are diode-clamped to that rail; the 100k from each pin limits the current.
ESD CLAMPS (HEADER SIDE)

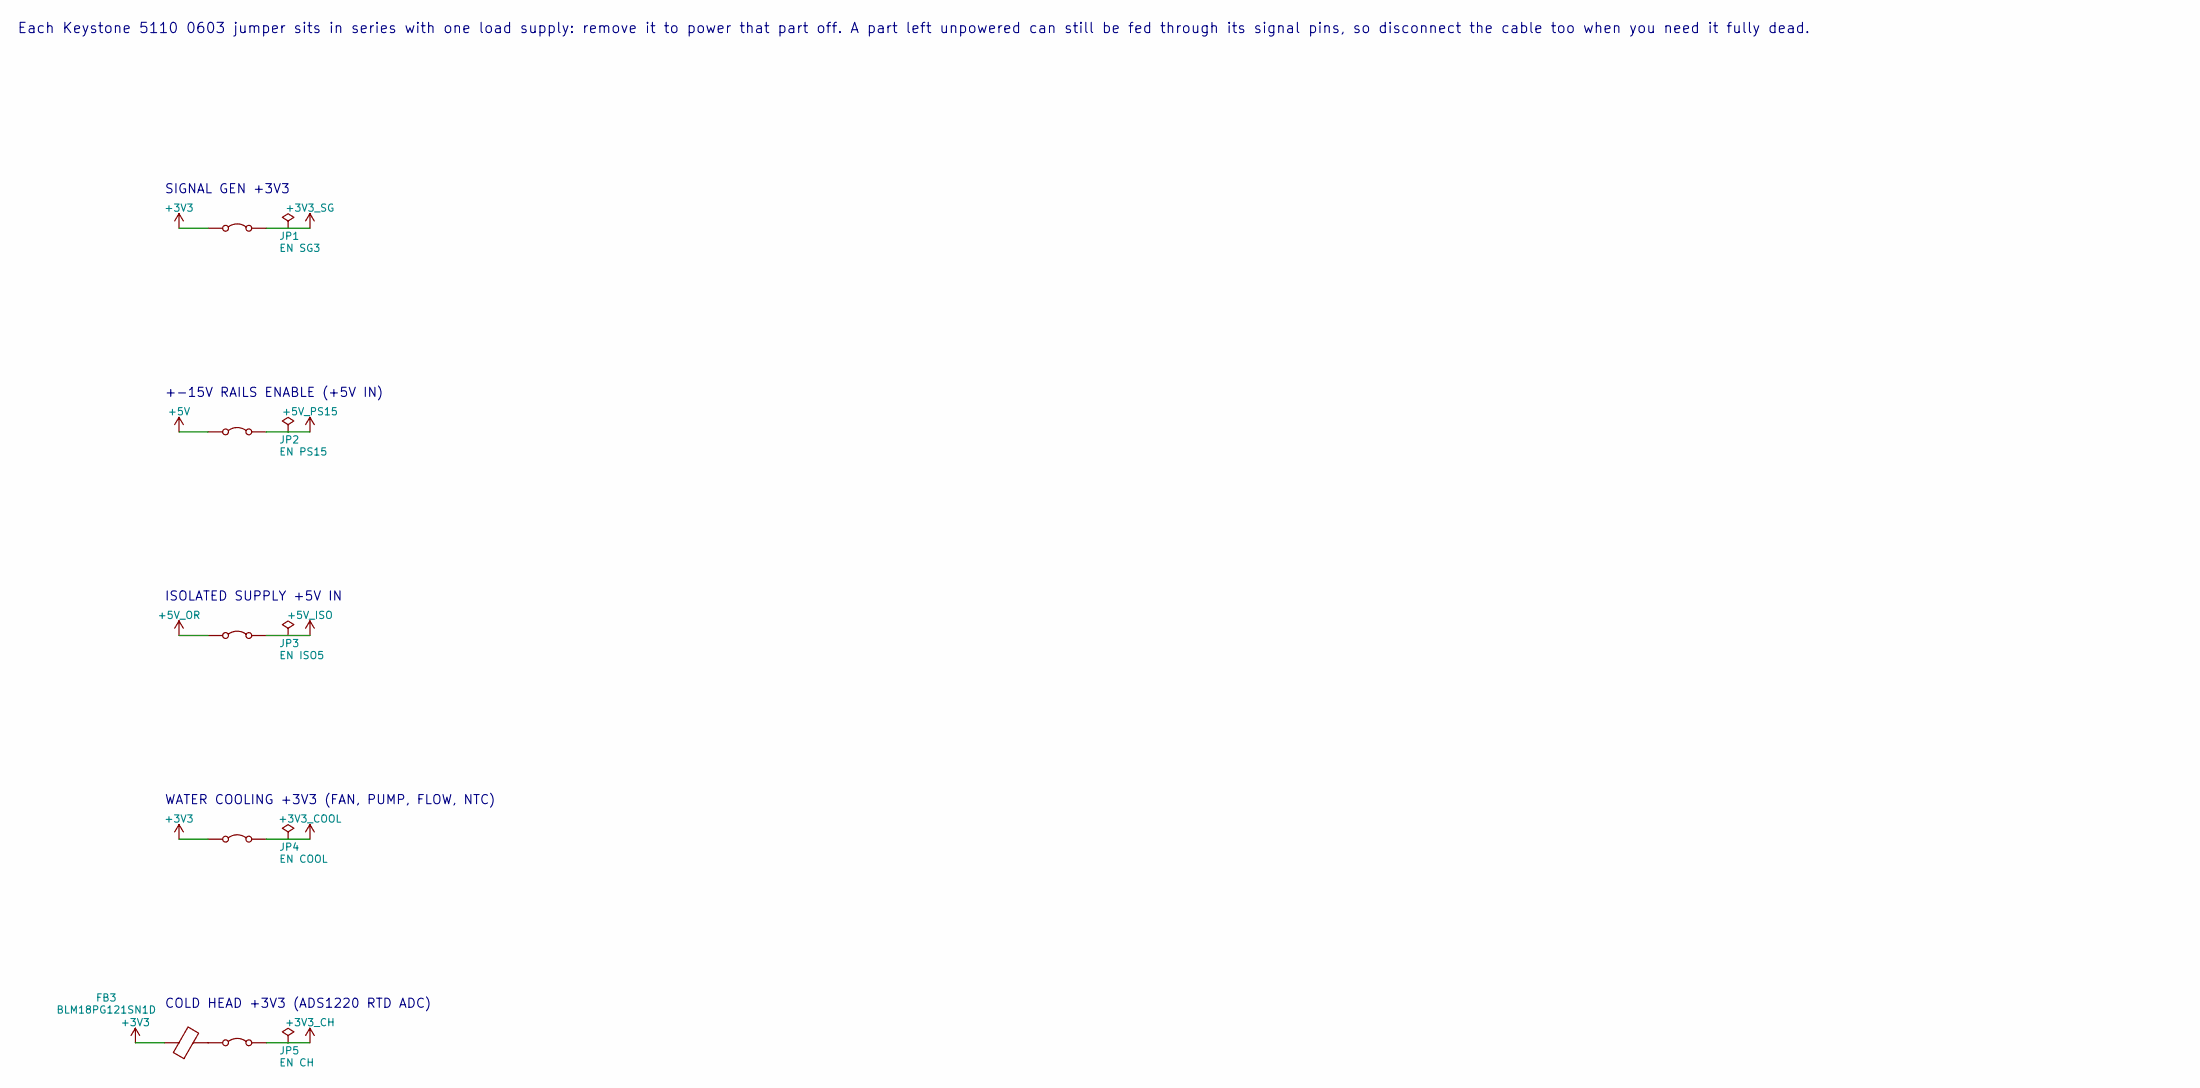
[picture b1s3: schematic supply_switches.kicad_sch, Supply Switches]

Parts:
FB3: BLM18PG121SN1D; L_0603_1608Metric
JP1: EN SG3; R_0603_1608Metric
JP2: EN PS15; R_0603_1608Metric
JP3: EN ISO5; R_0603_1608Metric
JP4: EN COOL; R_0603_1608Metric
JP5: EN CH; R_0603_1608Metric

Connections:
+3V3: FB3.1, JP1.1 (A), JP4.1 (A); also elsewhere on the board
+3V3_CH: JP5.2 (B); also elsewhere on the board
+3V3_COOL: JP4.2 (B); also elsewhere on the board
+3V3_SG: JP1.2 (B); also elsewhere on the board
+5V: JP2.1 (A); also elsewhere on the board
+5V_ISO: JP3.2 (B); also elsewhere on the board
+5V_OR: JP3.1 (A); also elsewhere on the board
+5V_PS15: JP2.2 (B); also elsewhere on the board
unnamed: FB3.2, JP5.1 (A)

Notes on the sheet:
Each Keystone 5110 0603 jumper sits in series with one load supply: remove it to power that part off. A part left unpowered can still be fed through its signal pins, so disconnect the cable too when you need it fully dead.
COLD HEAD +3V3 (ADS1220 RTD ADC)
WATER COOLING +3V3 (FAN, PUMP, FLOW, NTC)
SIGNAL GEN +3V3
ISOLATED SUPPLY +5V IN
+-15V RAILS ENABLE (+5V IN)
